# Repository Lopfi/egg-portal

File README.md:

# egg-portal
Automatic door for chicken huts

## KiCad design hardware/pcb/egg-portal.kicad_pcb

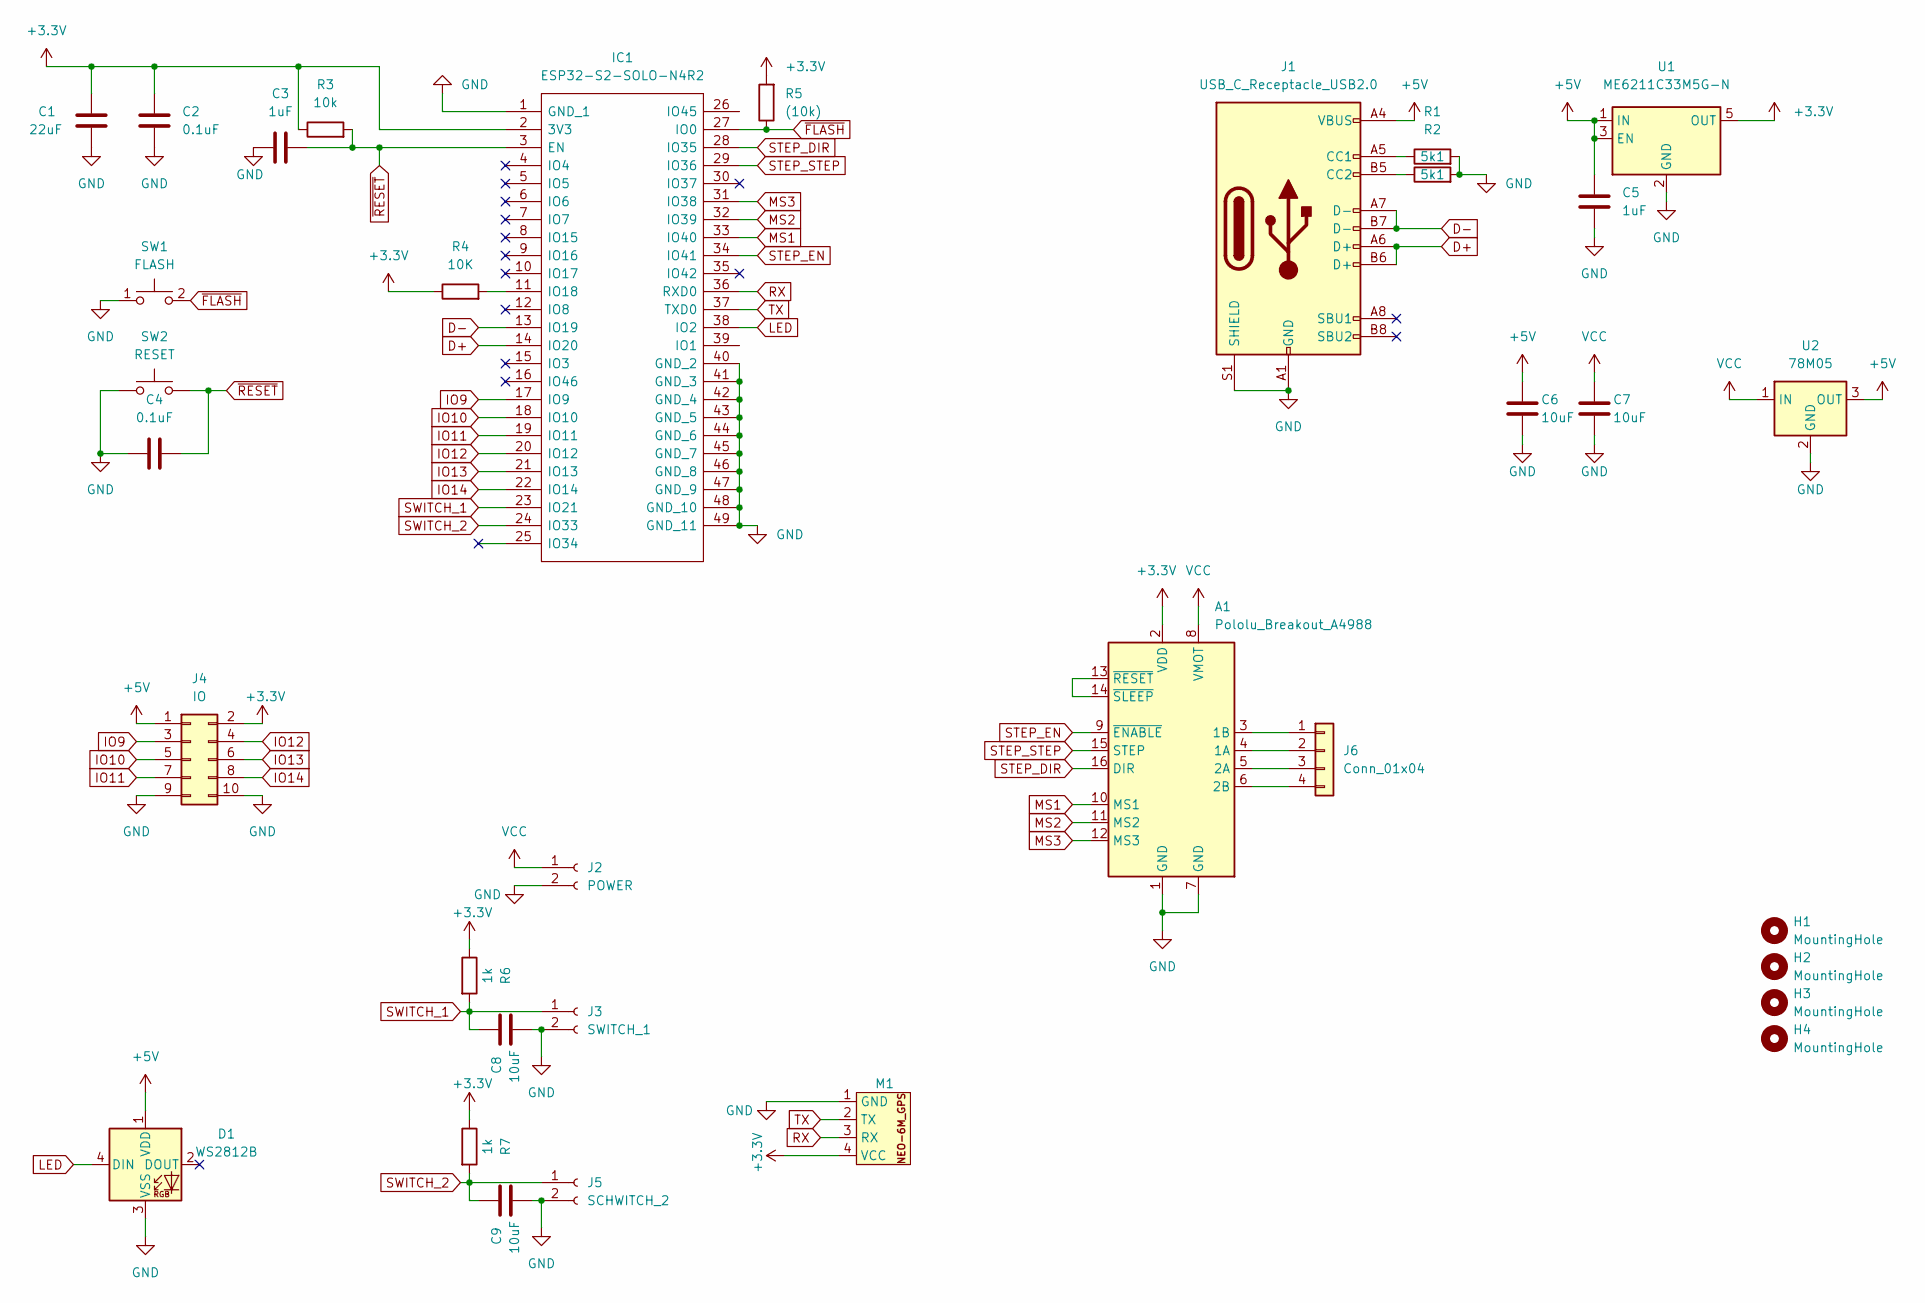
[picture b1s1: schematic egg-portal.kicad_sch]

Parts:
A1: Pololu_Breakout_A4988; A4988
C1: 22uF; C_0805_2012Metric_Pad1.18x1.45mm_HandSolder
C2, C4: 0.1uF; C_0805_2012Metric_Pad1.18x1.45mm_HandSolder
C3, C5: 1uF; C_0805_2012Metric_Pad1.18x1.45mm_HandSolder
C6, C7, C8, C9: 10uF; C_0603_1608Metric_Pad1.08x0.95mm_HandSolder
D1: WS2812B; LED_WS2812B_PLCC4_5.0x5.0mm_P3.2mm
H1, H2, H3, H4: MountingHole; MountingHole_2.2mm_M2
IC1: ESP32-S2-SOLO-N4R2; ESP32S2SOLON4R2; Manufacturer_Part_Number ESP32-S2-SOLO-N4R2; Mouser Part Number 356-ESP32-S2SOLON4R2
J1: USB_C_Receptacle_USB2.0; USB_C_Receptacle_HRO_TYPE-C-31-M-12
J2: POWER; TerminalBlock_Phoenix_MKDS-3-2-5.08_1x02_P5.08mm_Horizontal
J3: SWITCH_1; TerminalBlock_Phoenix_MKDS-3-2-5.08_1x02_P5.08mm_Horizontal
J4: IO; PinHeader_2x05_P2.54mm_Vertical
J5: SCHWITCH_2; TerminalBlock_Phoenix_MKDS-3-2-5.08_1x02_P5.08mm_Horizontal
J6: Conn_01x04; JST_XH_B4B-XH-A_1x04_P2.50mm_Vertical
M1: NEO-6M_GPS
R1, R2: 5k1; R_0805_2012Metric_Pad1.20x1.40mm_HandSolder
R3: 10k; R_0805_2012Metric_Pad1.20x1.40mm_HandSolder
R4: 10K; R_0805_2012Metric_Pad1.20x1.40mm_HandSolder
R5: (10k); R_0805_2012Metric_Pad1.20x1.40mm_HandSolder
R6, R7: 1k; R_0402_1005Metric_Pad0.72x0.64mm_HandSolder
SW1: FLASH; TS1187ABAB
SW2: RESET; TS1187ABAB
U1: ME6211C33M5G-N; SOT-23-5_HandSoldering
U2: 78M05; TO-252-2

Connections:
+3.3V: A1.2 (VDD), C1.2, C2.2, IC1.2 (3V3), J4.2, M1.4 (VCC), R3.1, R4.1, R5.2, R6.1, R7.1, U1.5 (OUT)
+5V: C5.1, C6.2, D1.1 (VDD), J1.A4 (VBUS), J1.A9 (VBUS), J1.B4 (VBUS), J1.B9 (VBUS), U1.1 (IN), U1.3 (EN), U2.3 (OUT)
D+: IC1.14 (IO20), J1.A6 (D+), J1.B6 (D+)
D-: IC1.13 (IO19), J1.A7 (D-), J1.B7 (D-)
GND: A1.1 (GND), A1.7 (GND), C1.1, C2.1, C3.1, C4.2, C5.2, C6.1, C7.1, C8.1, C9.1, D1.3 (VSS), IC1.1 (GND_1), IC1.40 (GND_2), IC1.41 (GND_3), IC1.42 (GND_4), IC1.43 (GND_5), IC1.44 (GND_6), IC1.45 (GND_7), IC1.46 (GND_8), IC1.47 (GND_9), IC1.48 (GND_10), IC1.49 (GND_11), J1.A1 (GND), J1.A12 (GND), J1.B1 (GND), J1.B12 (GND), J1.S1 (SHIELD), J2.2, J3.2, J4.9, J4.10, J5.2, M1.1 (GND), R1.2, R2.2, SW1.1, SW2.1, U1.2 (GND), U2.2 (GND)
IO9: IC1.17 (IO9), J4.3
IO10: IC1.18 (IO10), J4.5
IO11: IC1.19 (IO11), J4.7
IO12: IC1.20 (IO12), J4.4
IO13: IC1.21 (IO13), J4.6
IO14: IC1.22 (IO14), J4.8
LED: D1.4 (DIN), IC1.38 (IO2)
MS1: A1.10 (MS1), IC1.33 (IO40)
MS2: A1.11 (MS2), IC1.32 (IO39)
MS3: A1.12 (MS3), IC1.31 (IO38)
unnamed: A1.4 (1A), J6.2
unnamed: A1.3 (1B), J6.1
unnamed: A1.5 (2A), J6.3
unnamed: A1.6 (2B), J6.4
unnamed: A1.13 (~RESET), A1.14 (~SLEEP)
unnamed: IC1.11 (IO18), R4.2
unnamed: J1.A5 (CC1), R1.1
unnamed: J1.B5 (CC2), R2.1
RX: IC1.36 (RXD0), M1.3 (RX)
STEP_DIR: A1.16 (DIR), IC1.28 (IO35)
STEP_EN: A1.9 (~ENABLE), IC1.34 (IO41)
STEP_STEP: A1.15 (STEP), IC1.29 (IO36)
SWITCH_1: C8.2, IC1.23 (IO21), J3.1, R6.2
SWITCH_2: C9.2, IC1.24 (IO33), J5.1, R7.2
TX: IC1.37 (TXD0), M1.2 (TX)
VCC: A1.8 (VMOT), C7.2, J2.1, U2.1 (IN)
~FLASH: IC1.27 (IO0), R5.1, SW1.2
~RESET: C3.2, C4.1, IC1.3 (EN), R3.2, SW2.2

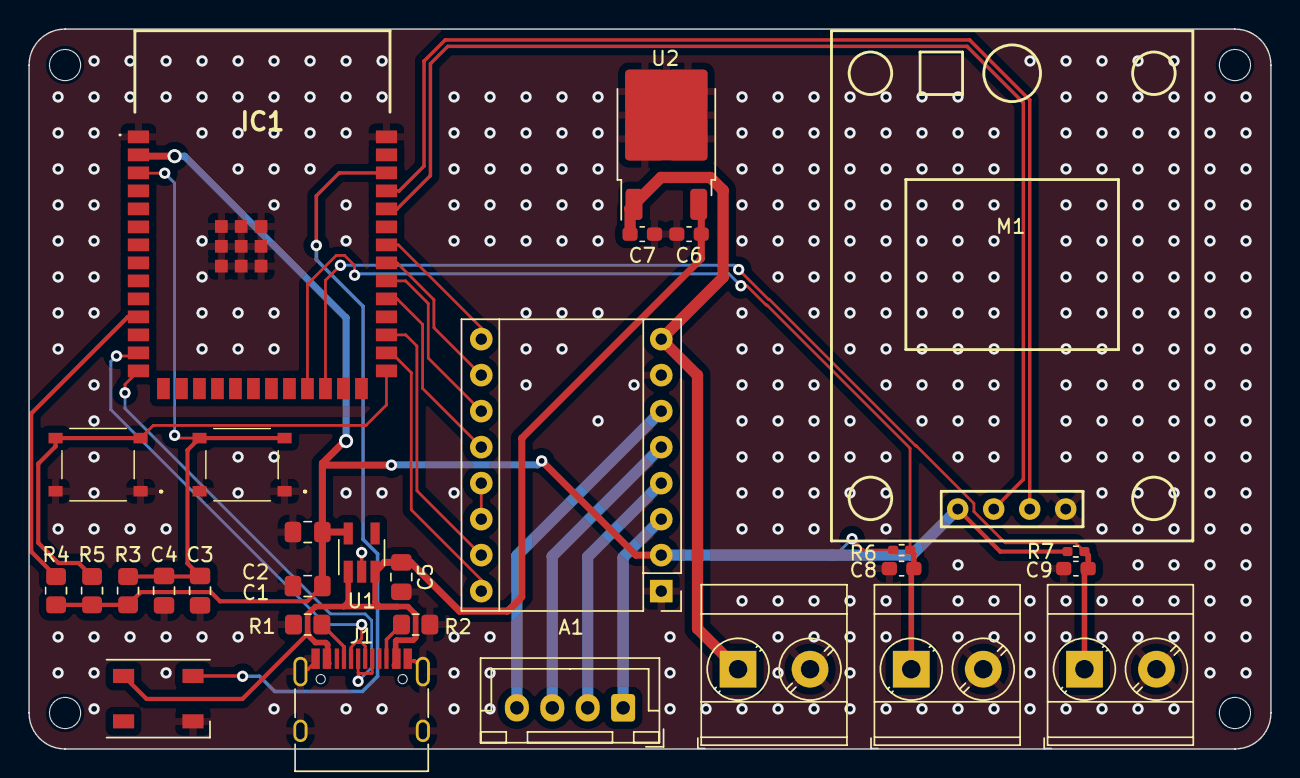
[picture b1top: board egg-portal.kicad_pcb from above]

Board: 2 copper layers, 87.6 x 50.8 mm, 33 parts (0 on the bottom side), 27 nets.

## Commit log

2023-12-01 init pio
2023-12-01 getting started
2023-12-04 start on test with wifi manager
2024-07-05 create PCB
2024-07-05 wip wifi firmware
2024-07-05 wip on firmware
2024-07-16 get basics working with gps
2024-11-07 start on neopixel implementation
